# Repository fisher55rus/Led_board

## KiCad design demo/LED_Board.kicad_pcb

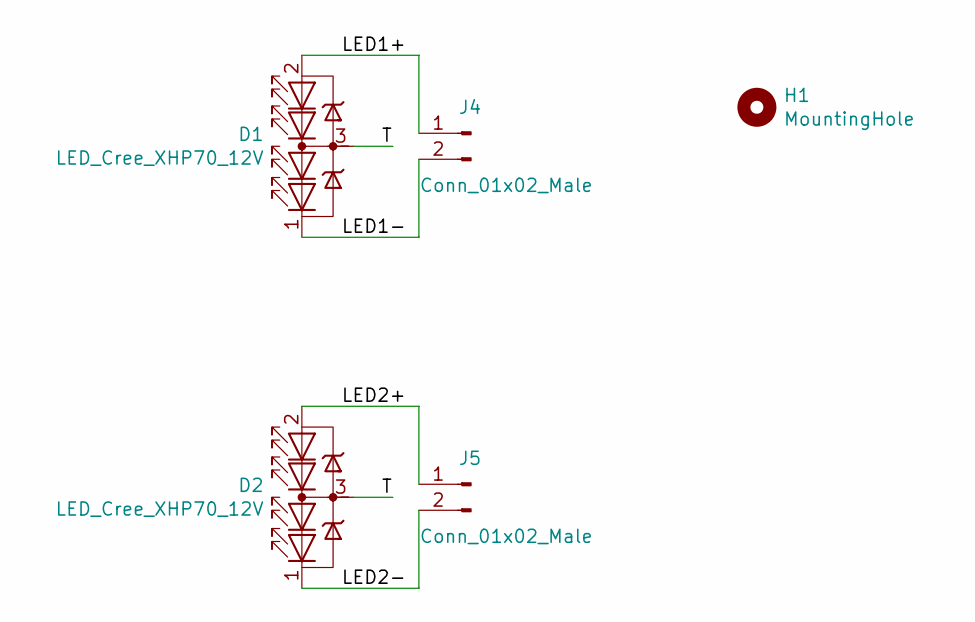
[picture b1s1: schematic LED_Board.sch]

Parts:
D1, D2: LED_Cree_XHP70_12V; LED_Cree-XHP70_12V
H1: MountingHole; MountingHole_5mm_Pad
J4, J5: Conn_01x02_Male; PinHeader_1x02_P2.54mm_Vertical

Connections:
/LED1+: D1.2 (A), J4.1
/LED1-: D1.1 (K), J4.2
/LED2+: D2.2 (A), J5.1
/LED2-: D2.1 (K), J5.2
/T: D1.3 (PAD), D2.3 (PAD)

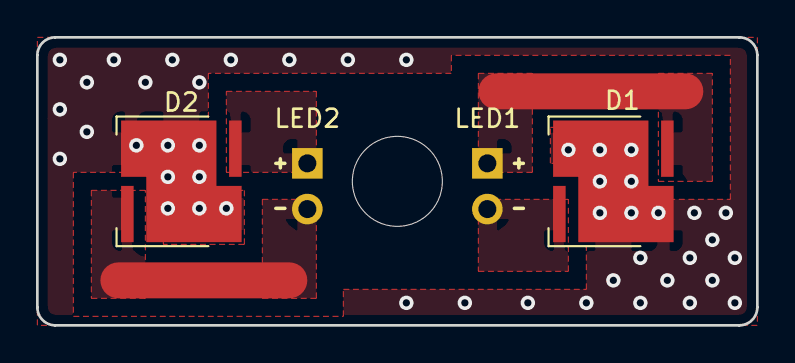
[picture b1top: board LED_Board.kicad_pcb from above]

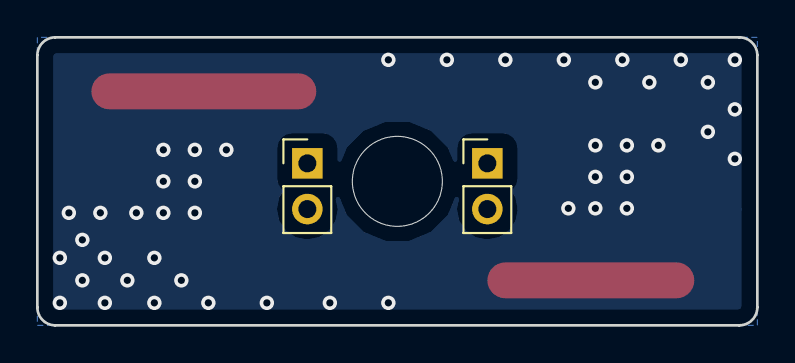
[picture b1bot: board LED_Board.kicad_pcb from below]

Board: 2 copper layers, 40.0 x 16.0 mm, 5 parts (2 on the bottom side), 5 nets.

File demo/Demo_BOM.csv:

¹;Component;Name;Quantity;Footprint
1;H1;MountingHole_5mm;1;MountingHole
2;J4,J5;PinHeader_1x02_P2.54mm_Vertical;2;Conn_01x02_Male
3;D1,D2;LED_Cree-XHP70_12V;2;LED_Cree_XHP70_12V

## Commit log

2019-04-04 Найдены 3d-модели, сделан набросок платы
2019-04-09 Завершена трассировка платы
2019-04-09 Предварительная трассировка демо-платы
2019-04-09 Закончена разводка платы
2019-04-27 Сформированы файлы BOM
